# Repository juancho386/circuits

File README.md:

# Circuits
Acá pongo las cosas que voy haciendo mientras aprendo sobre Raspberry Pi Pico, Arduino, ESP32 y tal vez algun otro board programable.

Cada directorio contiene un proyecto independiente. La idea es documentar todo lo posible pero vamos a ver si mi alterego me lo permite.

Todos los proyectos que ponga acá, son creados por mi. Así que los resultados de los tutoriales que vaya mirando para aprender definitivamente no.

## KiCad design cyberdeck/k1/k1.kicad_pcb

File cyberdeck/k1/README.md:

# K1: QWERTY keyboard para Pico

Teclado QWERTY con todas las teclas standard. El proyecto consta de 2 elementos:
- Circuito integrado PCB.
- Código en Arduino para programar un Raspberry Pico y emular el teclado.

> [!CAUTION]
> K1 es mi primer circuito que mando a imprimir. Aprendí de tutoriales en youtube y me animé. Puede contener errores de todo tipo. No me hago responsable de las consecuencias de ensamblarlo.

## Features:
- Tiene el ancho justo para complementar una pantalla de 4" (aproximadamente 9.6cm)
- Usa la tecla FN para extender teclas especiales como las teclas de función y las del keypad como insert, home, end, print screen, etc.
- Minimiza el espacio pero manteniendo una distancia adecuada para escribir con los pulgares.
- Lleva notación de todas las teclas posibles en la capa silk del PCB

### El PCB
De adelante

De atras

v1.0 built

#### Lista de materiales
- Raspberry Pi Pico
- 2 tiras de Connector 20xPin Headers
- 5x12-6 micro switches de 6x6x6
- 5+3 resistencias THT 0805 de 330Ω
- 4 LEDs

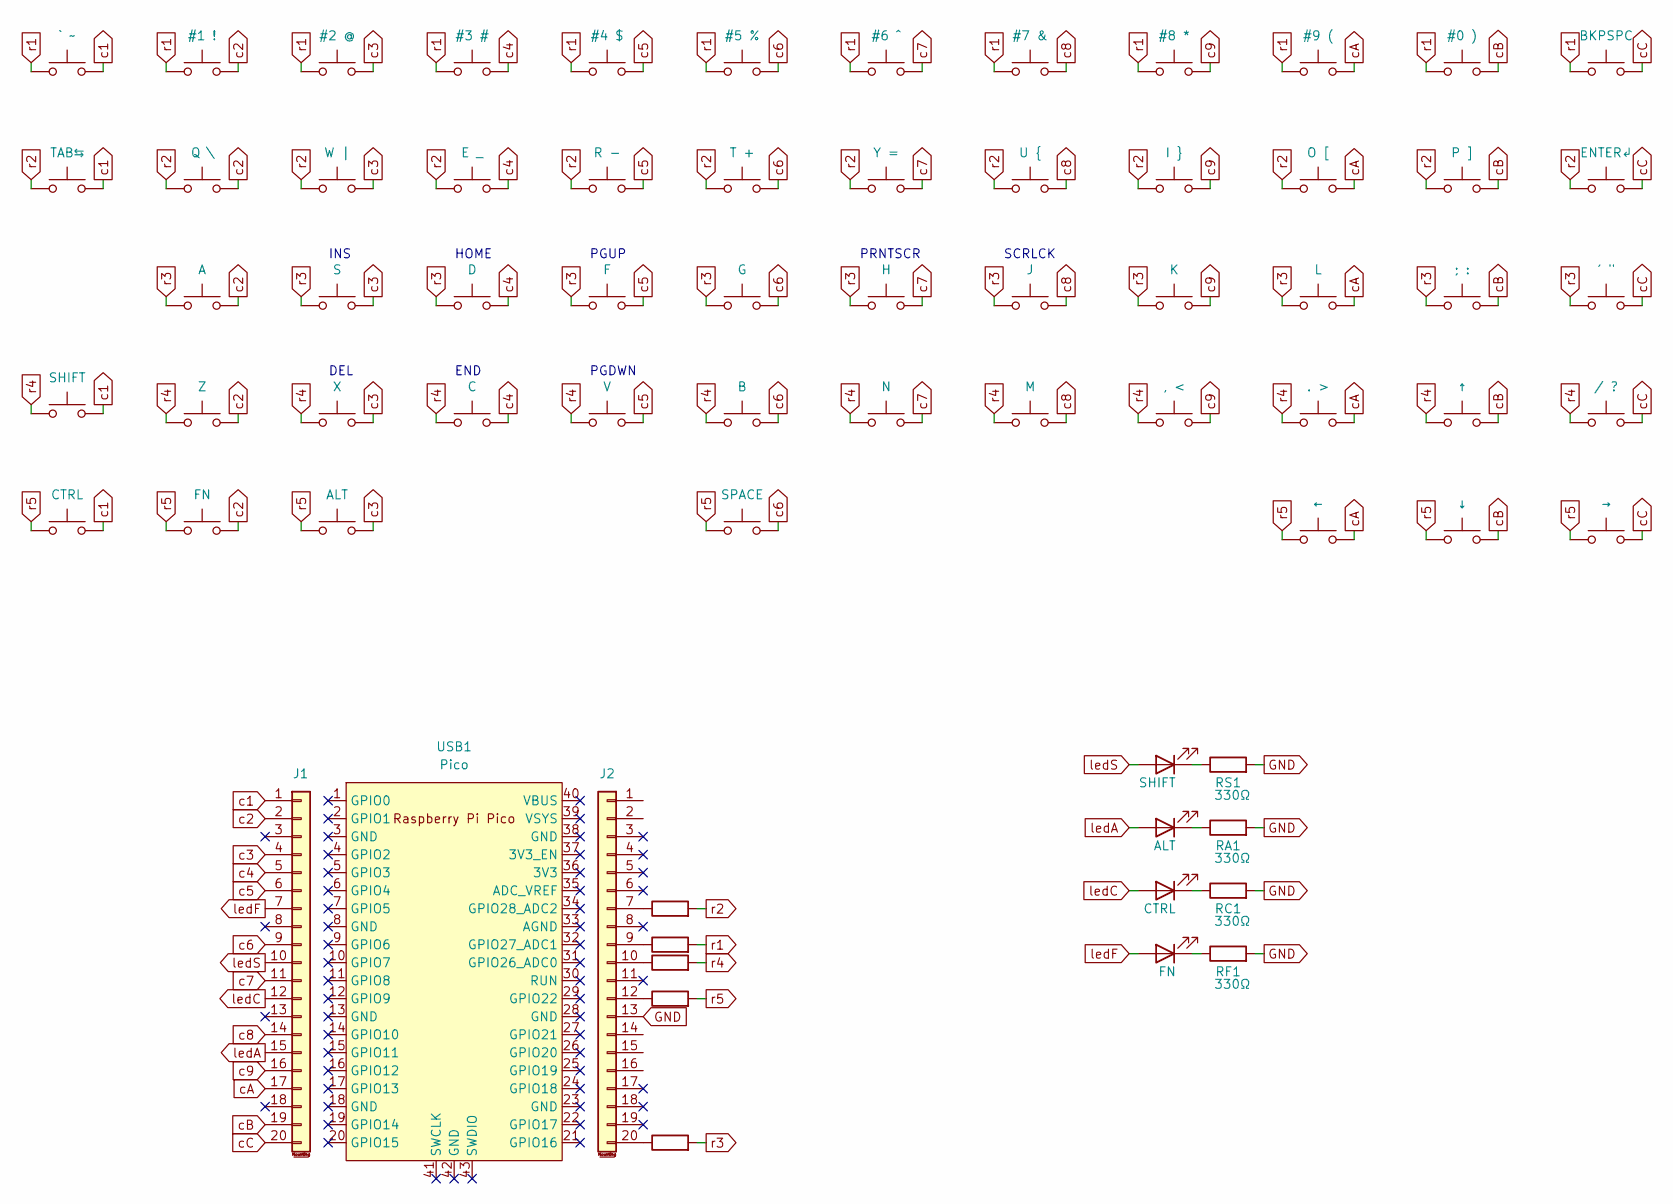
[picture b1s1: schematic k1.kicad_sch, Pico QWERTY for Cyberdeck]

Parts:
Dalt1: ALT; LED_D3.0mm
Dctrl1: CTRL; LED_D3.0mm
Dfn1: FN; LED_D3.0mm
Dshift1: SHIFT; LED_D3.0mm
J1, J2: Conn_01x20_MountingPin; PinHeader_1x20_P2.54mm_Vertical
RA1: 330Ω; R_0805_2012Metric_Pad1.20x1.40mm_HandSolder
RC1: 330Ω; R_0805_2012Metric_Pad1.20x1.40mm_HandSolder
RF1: 330Ω; R_0805_2012Metric_Pad1.20x1.40mm_HandSolder
RR1, RR2, RR3, RR4: R; R_0805_2012Metric_Pad1.20x1.40mm_HandSolder
RR5: 330ohn; R_0805_2012Metric_Pad1.20x1.40mm_HandSolder
RS1: 330Ω; R_0805_2012Metric_Pad1.20x1.40mm_HandSolder
SW0: #0 ); SW_PUSH_6mm
SW1: #1 !; SW_PUSH_6mm
SW2: #2 @; SW_PUSH_6mm
SW3: #3 #; SW_PUSH_6mm
SW4: #4 $; SW_PUSH_6mm
SW5: #5 %; SW_PUSH_6mm
SW6: #6 ^; SW_PUSH_6mm
SW7: #7 &; SW_PUSH_6mm
SW8: #8 *; SW_PUSH_6mm
SW9: #9 (; SW_PUSH_6mm
SW/1: / ?; SW_PUSH_6mm
SWa1: A; SW_PUSH_6mm
SWalt1: ALT; SW_PUSH_6mm
SWb1: B; SW_PUSH_6mm
SWc1: C; SW_PUSH_6mm
SWcoma1: , <; SW_PUSH_6mm
SWctrl1: CTRL; SW_PUSH_6mm
SWd1: D; SW_PUSH_6mm
SWdblquote1: ' "; SW_PUSH_6mm
SWdel1: BKPSPC; SW_PUSH_6mm
SWdown1: ↓; SW_PUSH_6mm
SWe1: E _; SW_PUSH_6mm
SWenter1: ENTER↲; SW_PUSH_6mm
SWf1: F; SW_PUSH_6mm
SWfn1: FN; SW_PUSH_6mm
SWg1: G; SW_PUSH_6mm
SWh1: H; SW_PUSH_6mm
SWi1: I }; SW_PUSH_6mm
SWj1: J; SW_PUSH_6mm
SWk1: K; SW_PUSH_6mm
SWl1: L; SW_PUSH_6mm
SWleft1: ←; SW_PUSH_6mm
SWm1: M; SW_PUSH_6mm
SWn1: N; SW_PUSH_6mm
SWo1: O [; SW_PUSH_6mm
SWp1: P ]; SW_PUSH_6mm
SWpunto1: . >; SW_PUSH_6mm
SWpuntoycoma1: ; :; SW_PUSH_6mm
SWq1: Q \; SW_PUSH_6mm
SWquote1: ` ~; SW_PUSH_6mm
SWr1: R -; SW_PUSH_6mm
SWright1: →; SW_PUSH_6mm
SWs1: S; SW_PUSH_6mm
SWshift1: SHIFT; SW_PUSH_6mm
SWspace1: SPACE; SW_PUSH_6mm
SWt1: T +; SW_PUSH_6mm
SWtab1: TAB⇆; SW_PUSH_6mm
SWu1: U {; SW_PUSH_6mm
SWup1: ↑; SW_PUSH_6mm
SWv1: V; SW_PUSH_6mm
SWw1: W |; SW_PUSH_6mm
SWx1: X; SW_PUSH_6mm
SWy1: Y =; SW_PUSH_6mm
SWz1: Z; SW_PUSH_6mm
USB1: Pico; RPi_Pico_SMD_TH

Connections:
GND: J2.13, RA1.2, RC1.2, RF1.2, RS1.2
unnamed: Dalt1.1 (K), RA1.1
unnamed: Dctrl1.1 (K), RC1.1
unnamed: Dfn1.1 (K), RF1.1
unnamed: Dshift1.1 (K), RS1.1
unnamed: J2.7, RR2.1
unnamed: J2.9, RR1.1
unnamed: J2.20, RR3.1
unnamed: J2.10, RR4.1
unnamed: J2.12, RR5.1
c1: J1.1, SWctrl1.2, SWquote1.2, SWshift1.2, SWtab1.2
c2: J1.2, SW1.2, SWa1.2, SWfn1.2, SWq1.2, SWz1.2
c3: J1.4, SW2.2, SWalt1.2, SWs1.2, SWw1.2, SWx1.2
c4: J1.5, SW3.2, SWc1.2, SWd1.2, SWe1.2
c5: J1.6, SW4.2, SWf1.2, SWr1.2, SWv1.2
c6: J1.9, SW5.2, SWb1.2, SWg1.2, SWspace1.2, SWt1.2
c7: J1.11, SW6.2, SWh1.2, SWn1.2, SWy1.2
c8: J1.14, SW7.2, SWj1.2, SWm1.2, SWu1.2
c9: J1.16, SW8.2, SWcoma1.2, SWi1.2, SWk1.2
cA: J1.17, SW9.2, SWl1.2, SWleft1.2, SWo1.2, SWpunto1.2
cB: J1.19, SW0.2, SWdown1.2, SWp1.2, SWpuntoycoma1.2, SWup1.2
cC: J1.20, SW/1.2, SWdblquote1.2, SWdel1.2, SWenter1.2, SWright1.2
ledA: Dalt1.2 (A), J1.15
ledC: Dctrl1.2 (A), J1.12
ledF: Dfn1.2 (A), J1.7
ledS: Dshift1.2 (A), J1.10
r1: RR1.2, SW0.1, SW1.1, SW2.1, SW3.1, SW4.1, SW5.1, SW6.1, SW7.1, SW8.1, SW9.1, SWdel1.1, SWquote1.1
r2: RR2.2, SWe1.1, SWenter1.1, SWi1.1, SWo1.1, SWp1.1, SWq1.1, SWr1.1, SWt1.1, SWtab1.1, SWu1.1, SWw1.1, SWy1.1
r3: RR3.2, SWa1.1, SWd1.1, SWdblquote1.1, SWf1.1, SWg1.1, SWh1.1, SWj1.1, SWk1.1, SWl1.1, SWpuntoycoma1.1, SWs1.1
r4: RR4.2, SW/1.1, SWb1.1, SWc1.1, SWcoma1.1, SWm1.1, SWn1.1, SWpunto1.1, SWshift1.1, SWup1.1, SWv1.1, SWx1.1, SWz1.1
r5: RR5.2, SWalt1.1, SWctrl1.1, SWdown1.1, SWfn1.1, SWleft1.1, SWright1.1, SWspace1.1

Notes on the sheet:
SCRLCK
PGUP
HOME
PGDWN
INS
DEL
END
PRNTSCR

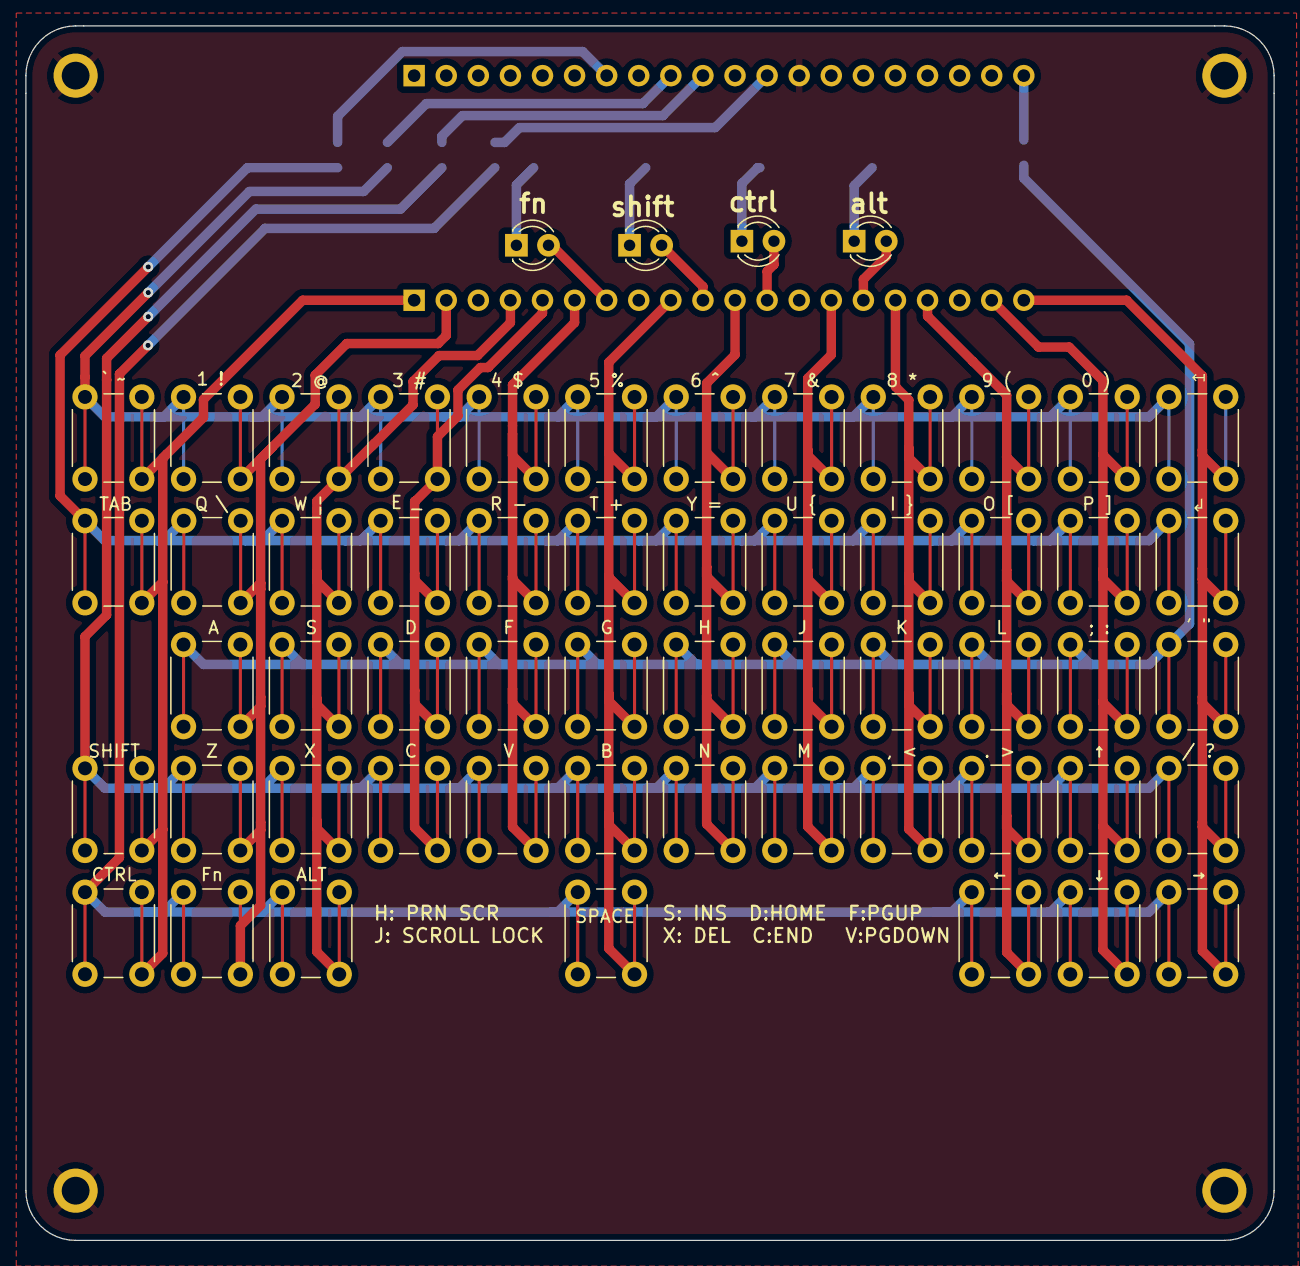
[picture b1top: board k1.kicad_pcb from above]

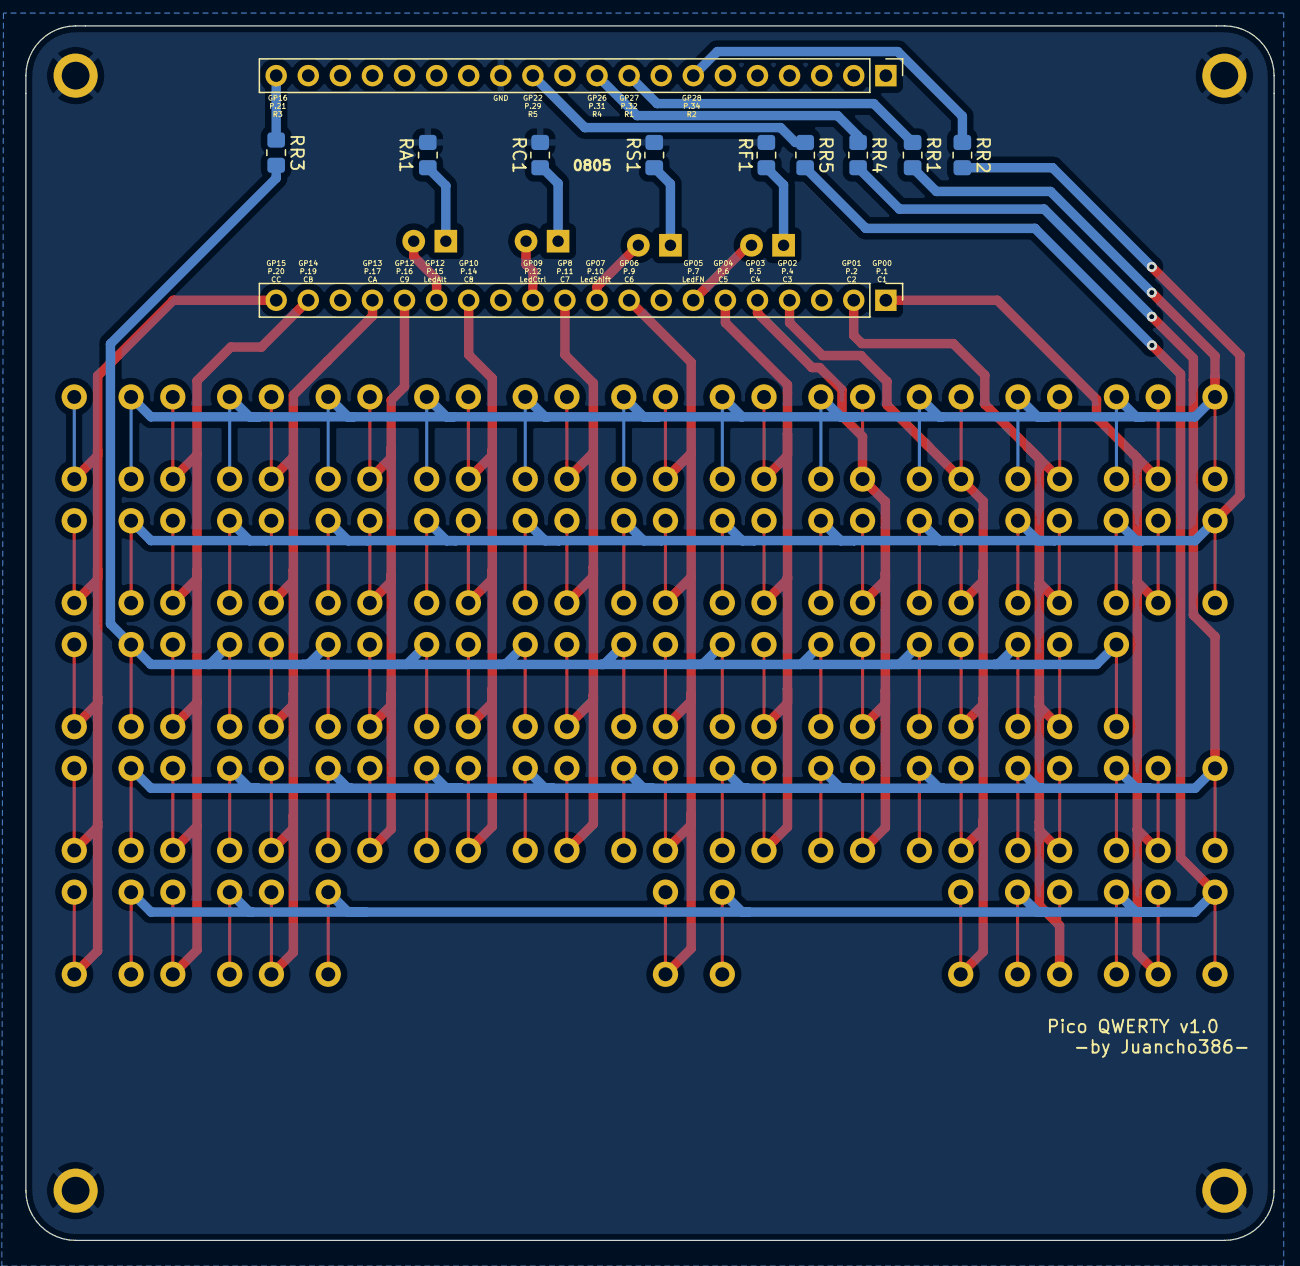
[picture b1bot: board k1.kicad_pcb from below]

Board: 2 copper layers, 98.8 x 96.1 mm, 69 parts (11 on the bottom side), 31 nets.

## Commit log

2024-11-27 empezamos a jugar con la electricidad tratando de no quemar nada ni morir en el intento
2024-11-27 para no olvidarme
2024-11-27 agregando fotito ilustrativa en el readme
2024-11-28 divehud
2024-11-28 cyberdeck
2024-11-28 cyberdeck req update
2024-12-03 teclado v1.0 creo que listo para pandar a imprimir
2024-12-03 evitamos subir caché y backups al pedo
2024-12-03 readme para el teclado
2024-12-03 cosas del teclado
2024-12-03 format readme
2024-12-04 posiblemente funcional
2024-12-04 MARK I: pcb mandado a imprimir a china a ver qué sale
2025-01-07 modificaciones para v1.1
2025-01-09 ahí lo armé. ahora viene el código y hacerlo andar
2025-01-09 achicando las fotos para que el readme quede mejor
2025-01-22 dos versiones de no-afk
2025-01-22 por ahora es PoC -porque anda para el culo-
